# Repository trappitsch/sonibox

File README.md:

# sonibox

A music box. Plays music from a specific folder when an RFID tag is placed on the reader.
If you want to build this, e.g., for your kid, I highly recommend to add more than 5 songs 
to any given playlist... or add more later ;)

## Approximate BOM, but you can use similar parts, vary as needed!

- [Raspberry Pi Pico 2040](https://www.raspberrypi.com/products/raspberry-pi-pico/)
- An MFRC522 RFID reader, e.g., [this one](https://www.velleman.eu/products/view/arduino-compatible-rfid-read-and-write-module-vma405/?id=435568&lang=en)
- [DFRobot Mini MP3 player](https://wiki.dfrobot.com/DFPlayer_Mini_SKU_DFR0299) and a microSD card with music
- [Speaker](https://www.digikey.ch/de/products/detail/pui-audio-inc/ASE06008MR-LW150-R/4700909)
- [Battery pack with charging circuit](https://www.dfrobot.com/product-2578.html)
- [Three triangle buttons](https://www.adafruit.com/product/4187)
- USB C panel mount to charge battery from outside
- Panel mount push button soldered to battery On/Off switch for external control
- Standoffs, screws, heat inserts, wires.
- PCB (see `pcb` folder)
- Laser cut enclosure (see `enclosure` folder)

## PCB 

The PCB is designed in KiCad, see the `pcb` folder. 
Production files for JLCPCB are in the `pcb/jlcpcb` folder. 
Assembly needs to be done by hand using through-hole components.

For the connectors you can use any 2.54mm pitch pin headers or 
similar sized Molex connectors (as a nice alternative).

## Enclosure

An outline of the enclosure is shown in the `enclosure` folder.
This is designed for 3mm acrylic. 
Many boxes are possible, this is just one example I liked.
Check out [this site](https://boxes.hackerspace-bamberg.de/) for more ideas!

## Firmware 

The firmware is written in Rust and uses 
[embassy](https://embassy.dev/) as the async executor. 
After 5 min of inactivity, the box will stop polling the RFID reader 
to save power, however, the current version does not put the MP3 player 
or the power button LED (if present) to sleep. A future version could however 
do that! However, using a beefy battery helps a lot even with these shortcomings.

A shout out to [1-rafael-1](https://github.com/1-rafael-1/), the maintainer of 
the [dfplayer-async](https://docs.rs/dfplayer-async/latest/dfplayer_async/) crate. 
Also a big thank you to the [embassy](https://embassy.dev/) team for this amazing tool 
and for fostering a very friendly and helpful community!

## Todo

- [ ] Add a watchdog to reset the Pico if some task gets stuck
- [ ] Add functionality to really put all power drawing components to sleep after inactivity (requires hardware mods)
- [ ] Add some better LED animations when the music plays. Something random? 

## License

This project is licensed under the MIT License - see the [LICENSE](LICENSE) file for details.

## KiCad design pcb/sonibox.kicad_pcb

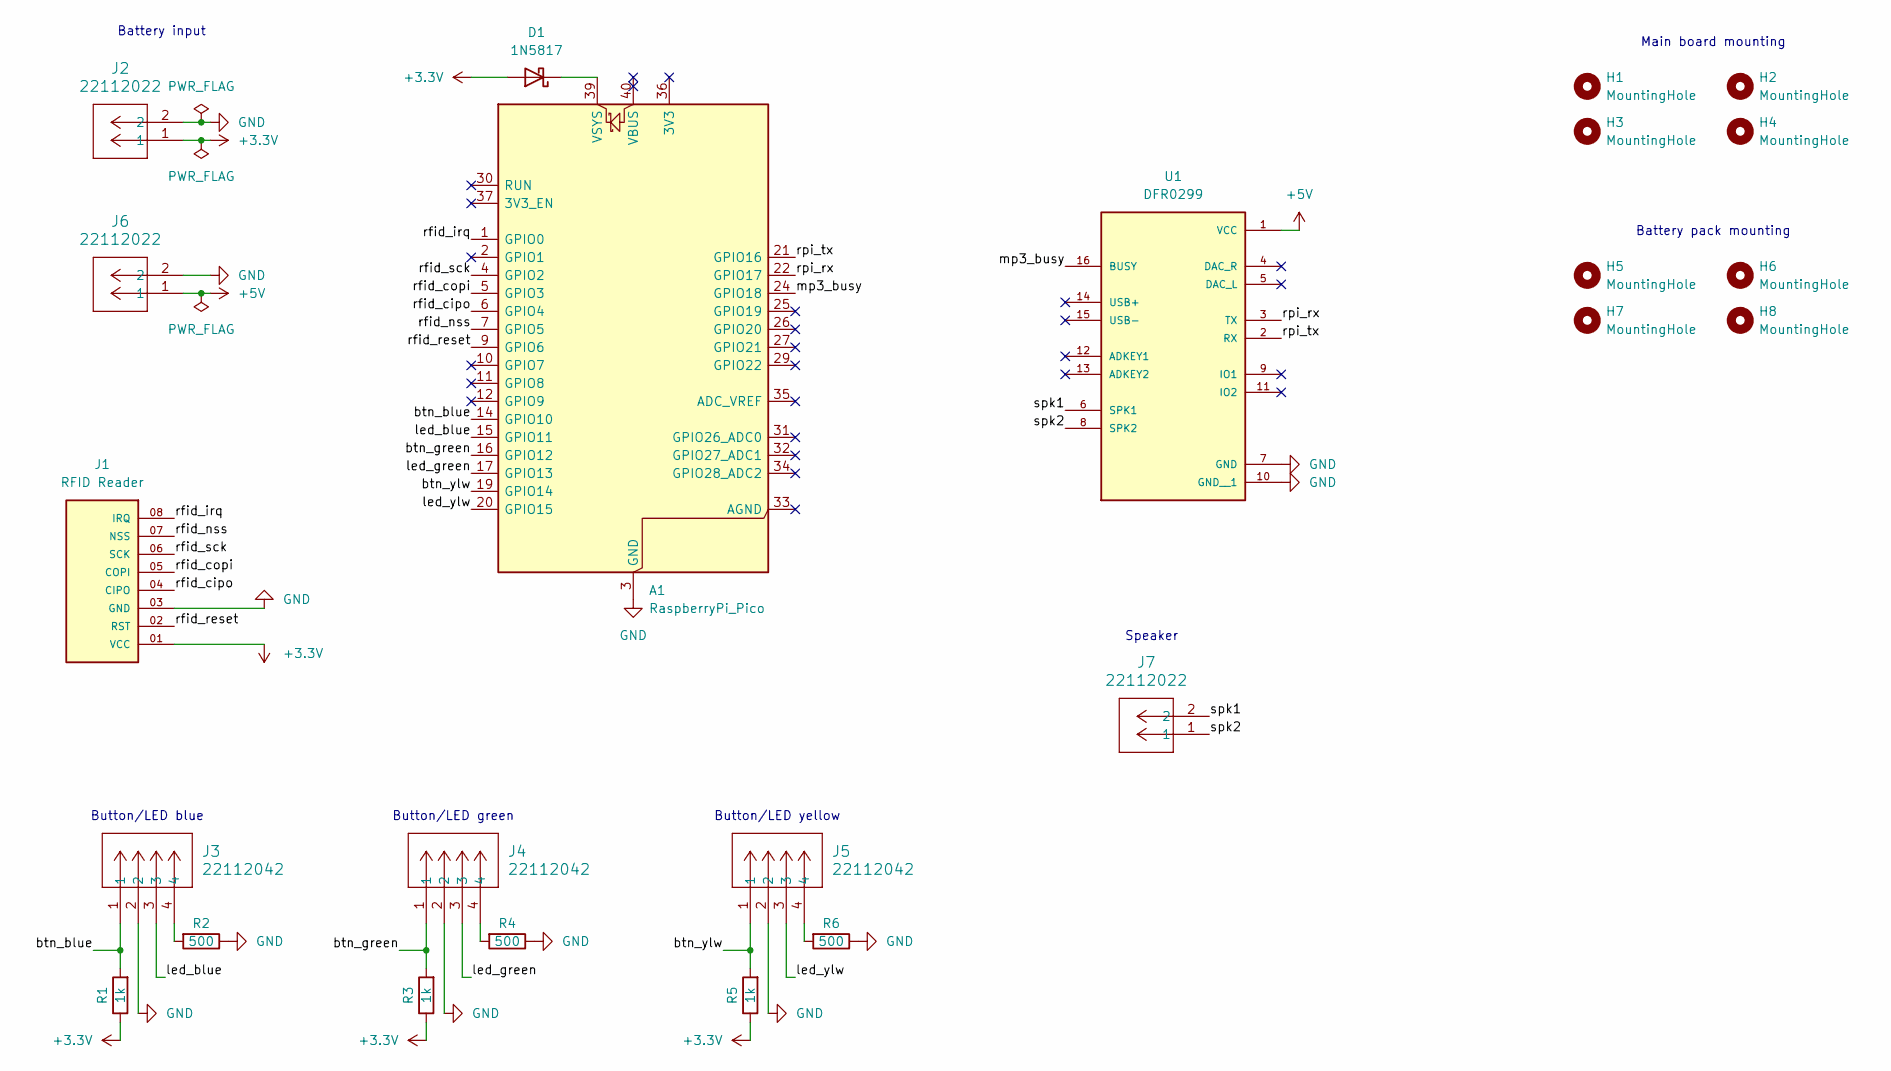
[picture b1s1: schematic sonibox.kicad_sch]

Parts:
A1: RaspberryPi_Pico; RaspberryPi_Pico_Common_Unspecified
D1: 1N5817; D_DO-41_SOD81_P10.16mm_Horizontal
H1, H2, H3, H4: MountingHole; MountingHole_3.2mm_M3
H5, H6, H7, H8: MountingHole; MountingHole_3mm
J1: RFID Reader; SAMTEC_TS-108-X-A-1; PARTREV B
J2, J6, J7: 22112022; CONN_A-6373-02A_MOL
J3, J4, J5: 22112042; CONN_A-6373-04A_MOL
R1, R3, R5: 1k; R_Axial_DIN0207_L6.3mm_D2.5mm_P10.16mm_Horizontal
R2, R4, R6: 500; R_Axial_DIN0207_L6.3mm_D2.5mm_P10.16mm_Horizontal
U1: DFR0299; MODULE_DFR0299

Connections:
+3.3V: D1.2 (A), J1.01 (VCC), J2.1, R1.1, R3.1, R5.1
+5V: J6.1, U1.1 (VCC)
/btn_blue: A1.14 (GPIO10), J3.1, R1.2
/btn_green: A1.16 (GPIO12), J4.1, R3.2
/btn_ylw: A1.19 (GPIO14), J5.1, R5.2
/led_blue: A1.15 (GPIO11), J3.3
/led_green: A1.17 (GPIO13), J4.3
/led_ylw: A1.20 (GPIO15), J5.3
/mp3_busy: A1.24 (GPIO18), U1.16 (BUSY)
/rfid_cipo: A1.6 (GPIO4), J1.04 (CIPO)
/rfid_copi: A1.5 (GPIO3), J1.05 (COPI)
/rfid_irq: A1.1 (GPIO0), J1.08 (IRQ)
/rfid_nss: A1.7 (GPIO5), J1.07 (NSS)
/rfid_reset: A1.9 (GPIO6), J1.02 (RST)
/rfid_sck: A1.4 (GPIO2), J1.06 (SCK)
/rpi_rx: A1.22 (GPIO17), U1.3 (TX)
/rpi_tx: A1.21 (GPIO16), U1.2 (RX)
/spk1: J7.2, U1.6 (SPK1)
/spk2: J7.1, U1.8 (SPK2)
GND: A1.3 (GND), A1.8 (GND), A1.13 (GND), A1.18 (GND), A1.23 (GND), A1.28 (GND), A1.38 (GND), J1.03 (GND), J2.2, J3.2, J4.2, J5.2, J6.2, R2.1, R4.1, R6.1, U1.7 (GND), U1.10 (GND__1)
unnamed: A1.39 (VSYS), D1.1 (K)
unnamed: J3.4, R2.2
unnamed: J4.4, R4.2
unnamed: J5.4, R6.2

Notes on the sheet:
Battery pack mounting
Speaker
Battery input
Button/LED blue
Button/LED green
Button/LED yellow
Main board mounting

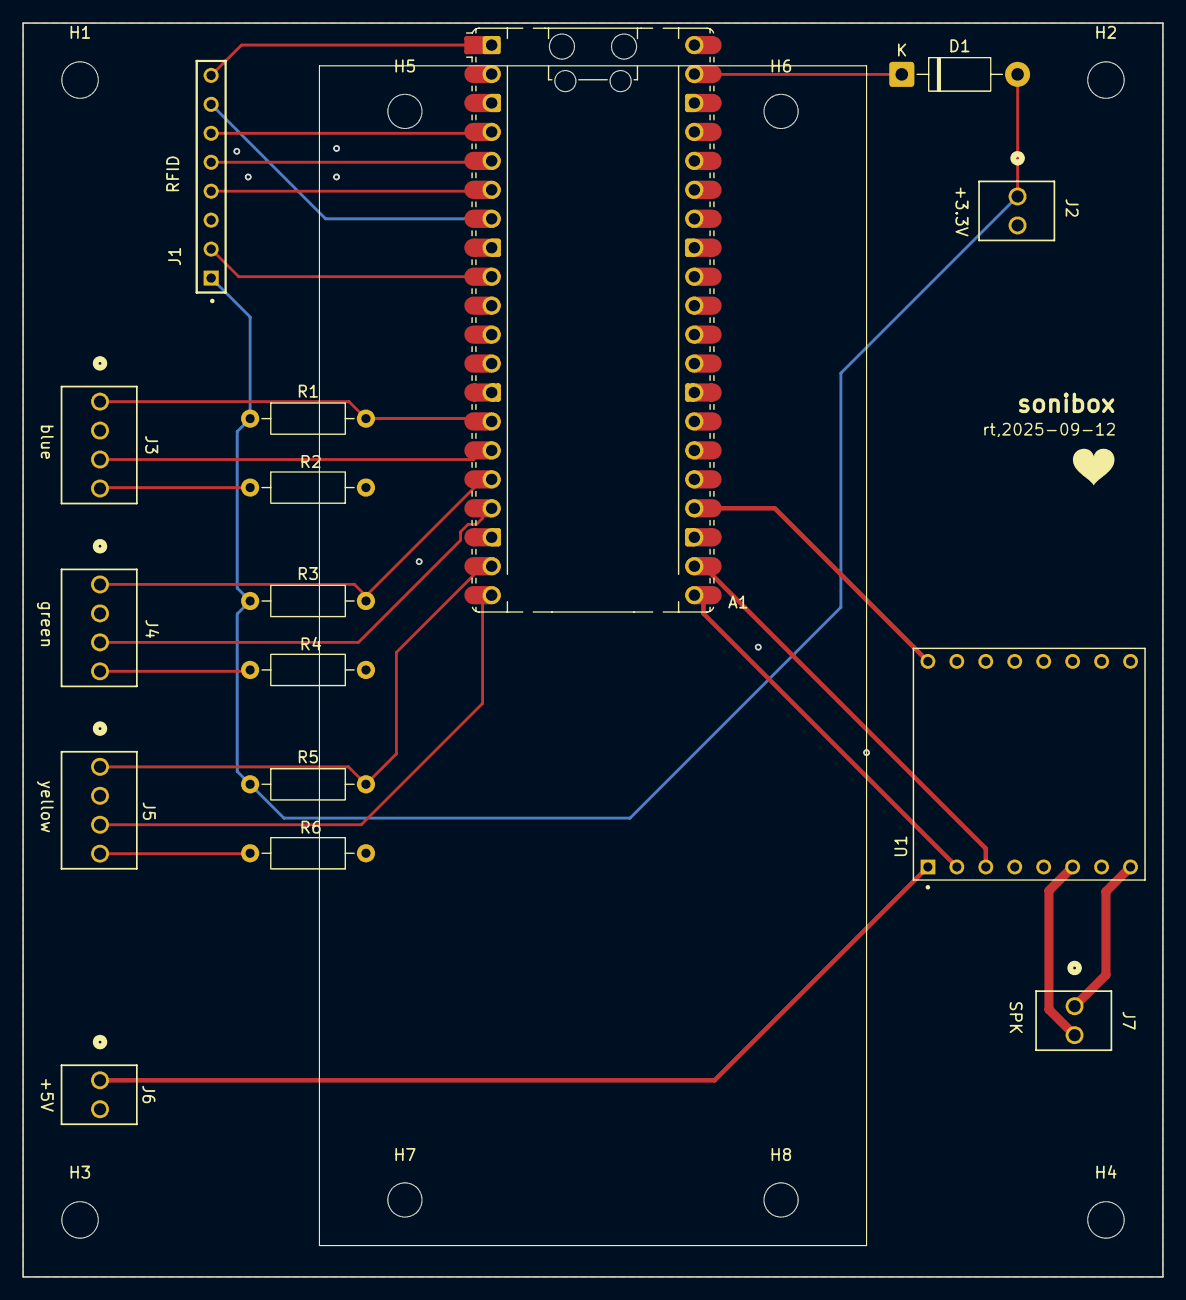
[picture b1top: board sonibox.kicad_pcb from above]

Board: 2 copper layers, 100.0 x 110.0 mm, 24 parts (0 on the bottom side), 24 nets.

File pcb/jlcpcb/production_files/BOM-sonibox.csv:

Comment,Designator,Footprint,LCSC,Quantity
500,R6,R_Axial_DIN0207_L6.3mm_D2.5mm_P10.16mm_Horizontal,,1
1k,R1,R_Axial_DIN0207_L6.3mm_D2.5mm_P10.16mm_Horizontal,,1
22112042,J5,CONN_A-6373-04A_MOL,,1
22112022,J7,CONN_A-6373-02A_MOL,,1
RFID Reader,J1,SAMTEC_TS-108-X-A-1,,1
22112022,J2,CONN_A-6373-02A_MOL,,1
1k,R3,R_Axial_DIN0207_L6.3mm_D2.5mm_P10.16mm_Horizontal,,1
500,R2,R_Axial_DIN0207_L6.3mm_D2.5mm_P10.16mm_Horizontal,,1
DFR0299,U1,MODULE_DFR0299,,1
22112042,J3,CONN_A-6373-04A_MOL,,1
22112022,J6,CONN_A-6373-02A_MOL,,1
22112042,J4,CONN_A-6373-04A_MOL,,1
1k,R5,R_Axial_DIN0207_L6.3mm_D2.5mm_P10.16mm_Horizontal,,1
RaspberryPi_Pico,A1,RaspberryPi_Pico_Common_Unspecified,,1
1N5817,D1,D_DO-41_SOD81_P10.16mm_Horizontal,,1
500,R4,R_Axial_DIN0207_L6.3mm_D2.5mm_P10.16mm_Horizontal,,1

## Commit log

2024-06-23 first version of rough box
2025-05-26 map over to esp32
2025-06-08 First rust version checkin - player is there
2025-06-11 buttons done
2025-06-11 started rfid task in its own module
2025-06-16 Add my RFID tags and write a folder selector for player folder
2025-06-22 integrate pretty much everything, dfplayer needs more work, likely on library
2025-07-03 finish mp3 player
2025-10-09 fix firmware with some features and leds, add kicad, add enclosure
2025-10-09 add readme and license
2026-02-20 Bump keccak from 0.1.5 to 0.1.6 in /sonibox-rs
    Bumps [keccak](https://github.com/RustCrypto/sponges) from 0.1.5 to 0.1.6.
    - [Commits](https://github.com/RustCrypto/sponges/compare/keccak-v0.1.5...keccak-v0.1.6)
    ---
    updated-dependencies:
    - dependency-name: keccak
    dependency-version: 0.1.6
